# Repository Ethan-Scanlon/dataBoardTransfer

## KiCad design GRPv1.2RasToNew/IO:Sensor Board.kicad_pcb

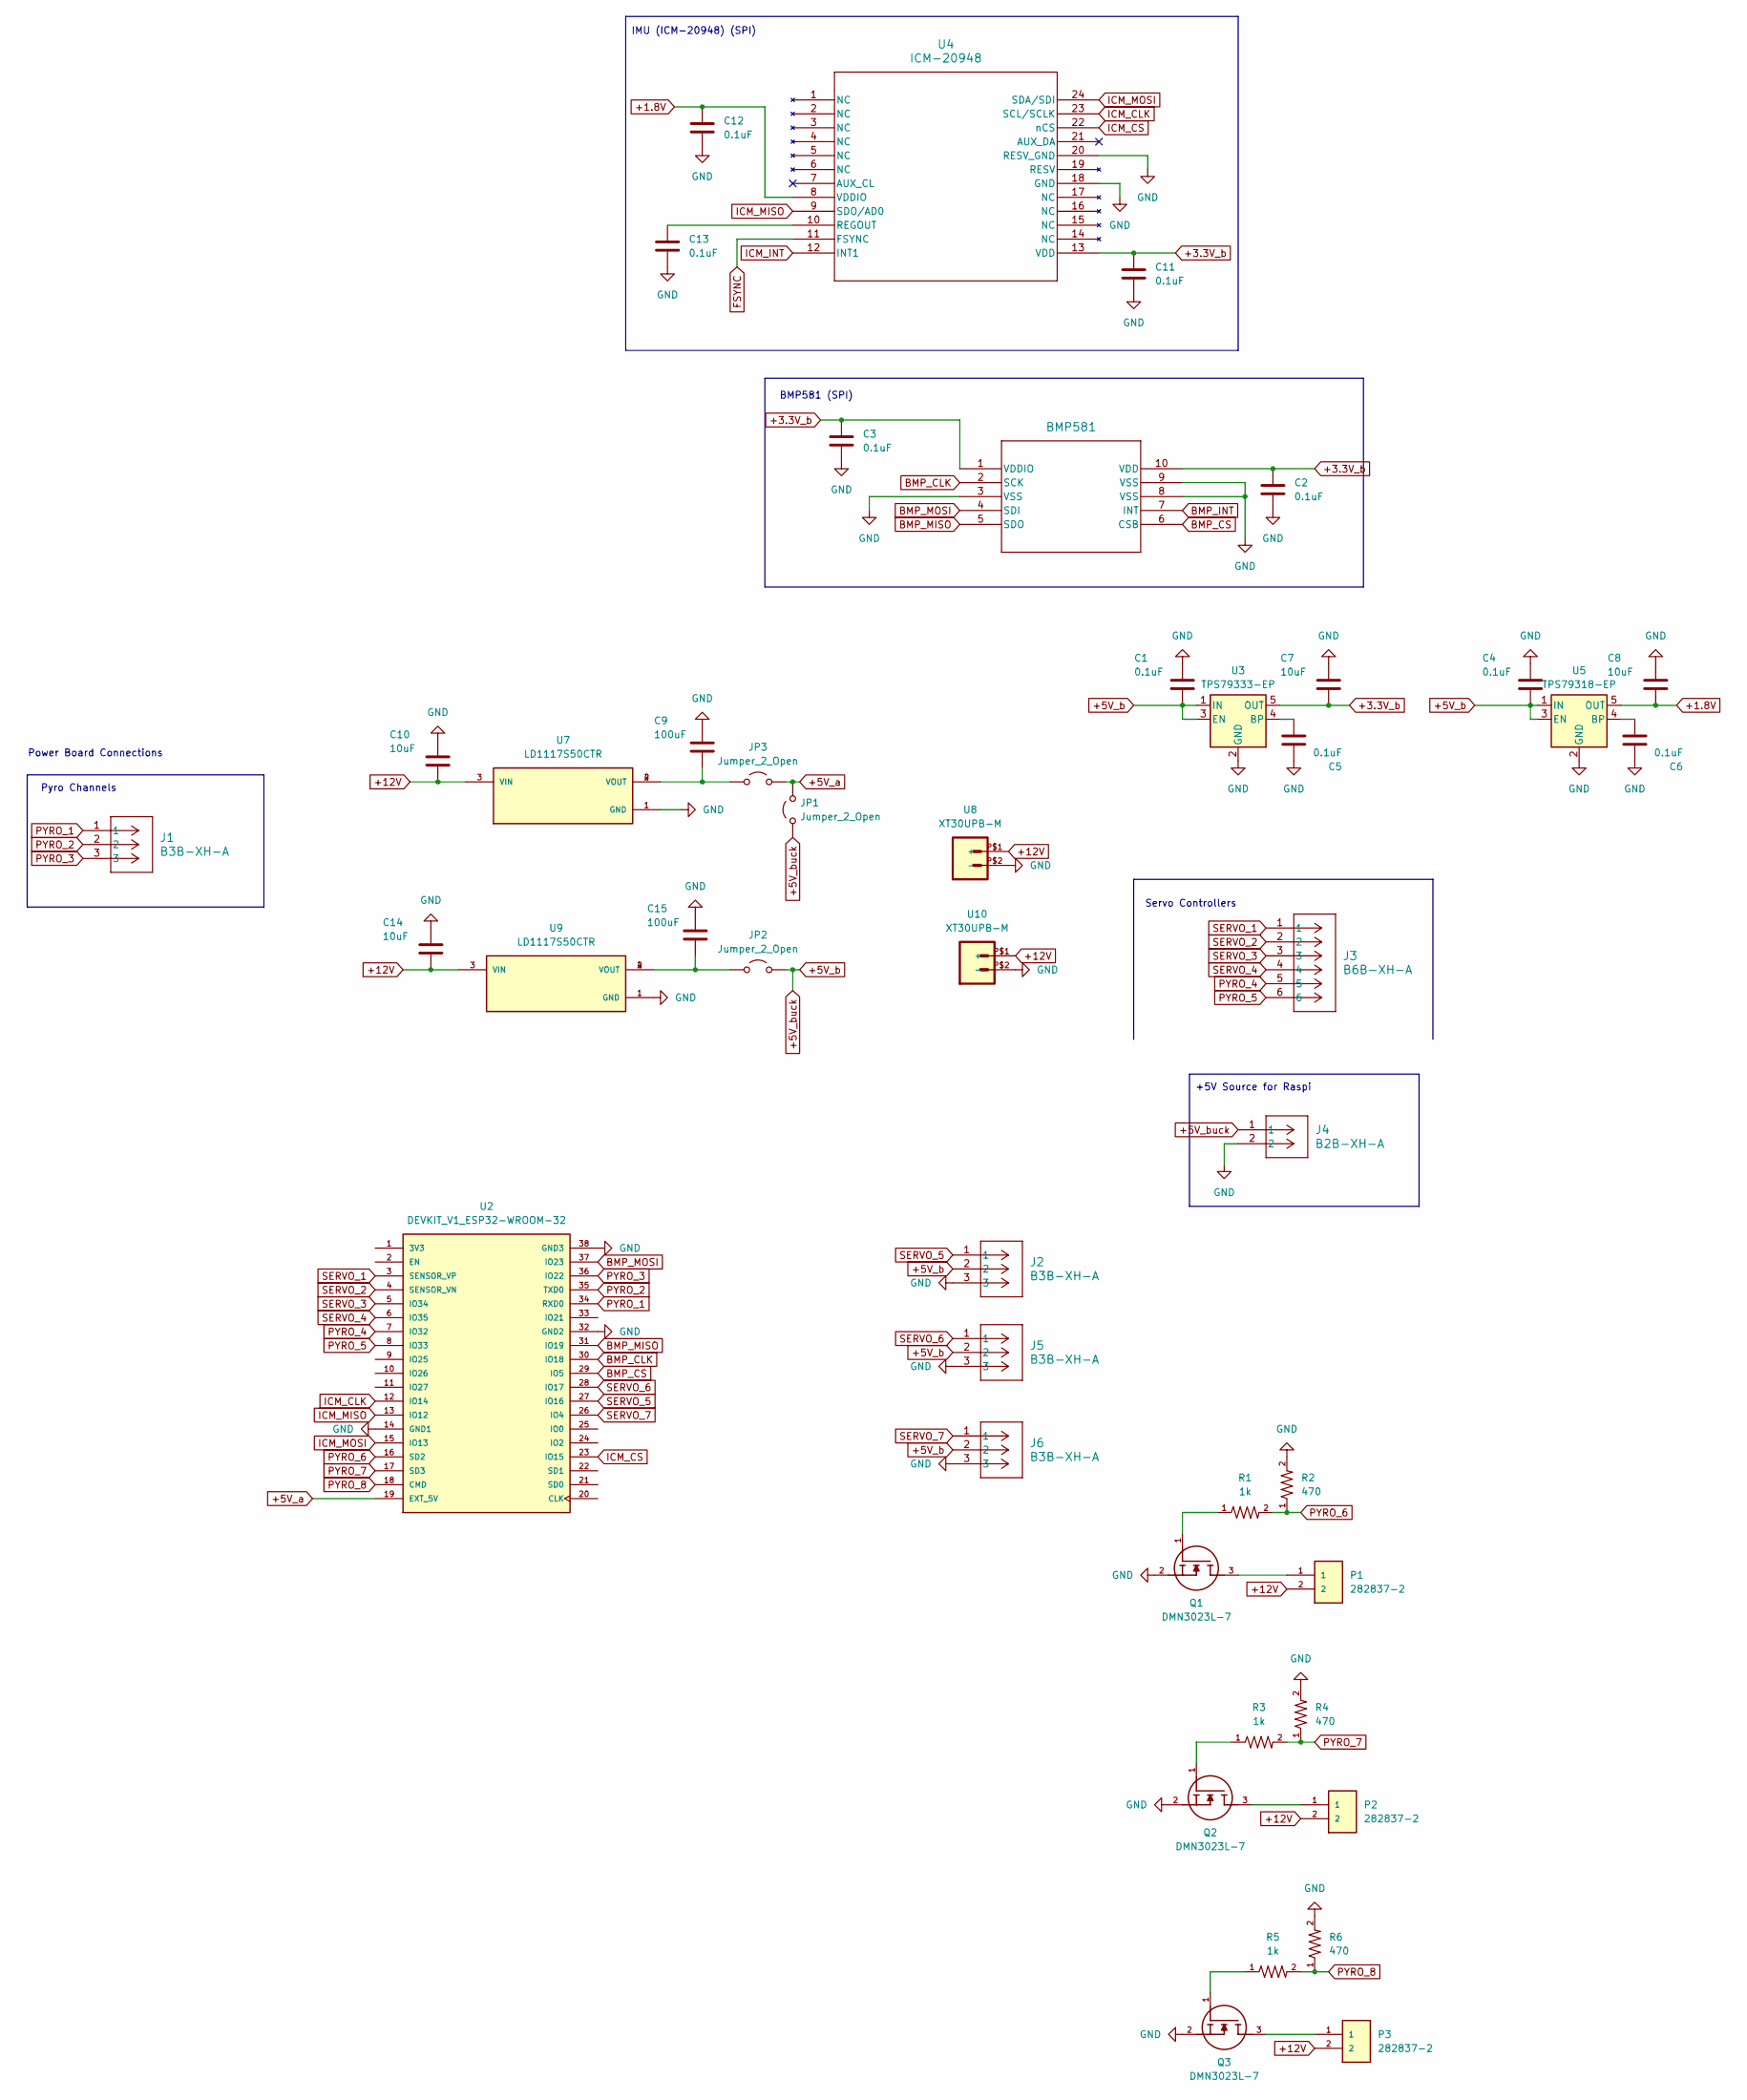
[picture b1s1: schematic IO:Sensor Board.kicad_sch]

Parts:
C1, C2, C3, C4, C5, C6, C11, C12, C13: 0.1uF; C_0805_2012Metric_Pad1.18x1.45mm_HandSolder
C7, C8, C10, C14: 10uF; C_0805_2012Metric_Pad1.18x1.45mm_HandSolder
C9, C15: 100uF; C_0805_2012Metric_Pad1.18x1.45mm_HandSolder
J1, J2, J5, J6: B3B-XH-A; CONN_B3B-XH-A_JST
J3: B6B-XH-A; JST_XH_B6B-XH-A_1x06_P2.50mm_Vertical
J4: B2B-XH-A; CONN_B2B-XH-A_JST
JP1, JP2, JP3: Jumper_2_Open; SolderJumper-2_P1.3mm_Open_RoundedPad1.0x1.5mm
P1, P2, P3: 282837-2; CUI_TB002-500-02BE; PARTREV G3
Q1, Q2, Q3: DMN3023L-7; SOT96P240X100-3N; MANUFACTURER_PART_NUMBER DMN3023L-7
R1, R3, R5: 1k; R_0805_2012Metric_Pad1.20x1.40mm_HandSolder
R2, R4, R6: 470; R_0805_2012Metric_Pad1.20x1.40mm_HandSolder
U1: BMP581; QFN10_BMP581_BOS
U2: DEVKIT_V1_ESP32-WROOM-32; MODULE_DEVKIT_V1_ESP32-WROOM-32; PARTREV N/A
U3: TPS79333-EP; SOT-23-5
U4: ICM-20948; QFN24_3X3X0P9_IVS
U5: TPS79318-EP; SOT-23-5
U7, U9: LD1117S50CTR; PARTREV 37
U8, U10: XT30UPB-M

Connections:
+1.8V: C8.2, C12.1, U4.8 (VDDIO), U5.5 (OUT)
+3.3V_b: C2.1, C3.1, C7.2, C11.1, U1.1 (VDDIO), U1.10 (VDD), U3.5 (OUT), U4.13 (VDD)
+5V_a: JP1.2 (B), JP3.2 (B), U2.19 (EXT_5V)
+5V_b: C1.2, C4.2, J2.2, J4.1, J5.2, J6.2, JP1.1 (A), JP2.2 (B), U3.1 (IN), U3.3 (EN), U5.1 (IN), U5.3 (EN)
+12V: C10.2, C14.2, P1.2, P2.2, P3.2, U7.3 (VIN), U8.P$1 (+), U9.3 (VIN), U10.P$1 (+)
BMP_CLK: U1.2 (SCK), U2.30 (IO18)
BMP_CS: U1.6 (CSB), U2.29 (IO5)
BMP_INT: U1.7 (INT)
BMP_MISO: U1.5 (SDO), U2.31 (IO19)
BMP_MOSI: U1.4 (SDI), U2.37 (IO23)
FSYNC: U4.11 (FSYNC)
GND: C1.1, C2.2, C3.2, C4.1, C5.1, C6.1, C7.1, C8.1, C9.1, C10.1, C11.2, C12.2, C13.2, C14.1, C15.1, J2.3, J4.2, J5.3, J6.3, Q1.2, Q2.2, Q3.2, R2.2, R4.2, R6.2, U1.3 (VSS), U1.8 (VSS), U1.9 (VSS), U2.14 (GND1), U2.32 (GND2), U2.38 (GND3), U3.2 (GND), U4.18 (GND), U4.20 (RESV_GND), U5.2 (GND), U7.1 (GND), U8.P$2 (-), U9.1 (GND), U10.P$2 (-)
ICM_CLK: U2.12 (IO14), U4.23 (SCL/SCLK)
ICM_CS: U2.23 (IO15), U4.22 (nCS)
ICM_INT: U4.12 (INT1)
ICM_MISO: U2.13 (IO12), U4.9 (SDO/AD0)
ICM_MOSI: U2.15 (IO13), U4.24 (SDA/SDI)
unnamed: C15.2, JP2.1 (A), U9.2 (VOUT), U9.4 (VOUT)
unnamed: C9.2, JP3.1 (A), U7.2 (VOUT), U7.4 (VOUT)
unnamed: P1.1, Q1.3
unnamed: P2.1, Q2.3
unnamed: P3.1, Q3.3
unnamed: Q1.1, R1.1
unnamed: Q2.1, R3.1
unnamed: Q3.1, R5.1
unnamed: C5.2, U3.4 (BP)
unnamed: C13.1, U4.10 (REGOUT)
unnamed: C6.2, U5.4 (BP)
PYRO_1: J1.1, U2.34 (RXD0)
PYRO_2: J1.2, U2.35 (TXD0)
PYRO_3: J1.3, U2.36 (IO22)
PYRO_4: J3.5, U2.7 (IO32)
PYRO_5: J3.6, U2.8 (IO33)
PYRO_6: R1.2, R2.1, U2.16 (SD2)
PYRO_7: R3.2, R4.1, U2.17 (SD3)
PYRO_8: R5.2, R6.1, U2.18 (CMD)
SERVO_1: J3.1, U2.3 (SENSOR_VP)
SERVO_2: J3.2, U2.4 (SENSOR_VN)
SERVO_3: J3.3, U2.5 (IO34)
SERVO_4: J3.4, U2.6 (IO35)
SERVO_5: J2.1, U2.27 (IO16)
SERVO_6: J5.1, U2.28 (IO17)
SERVO_7: J6.1, U2.26 (IO4)

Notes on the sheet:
+5V Source for Raspi
Pyro Channels
BMP581 (SPI)
IMU (ICM-20948) (SPI)
Power Board Connections
Servo Controllers

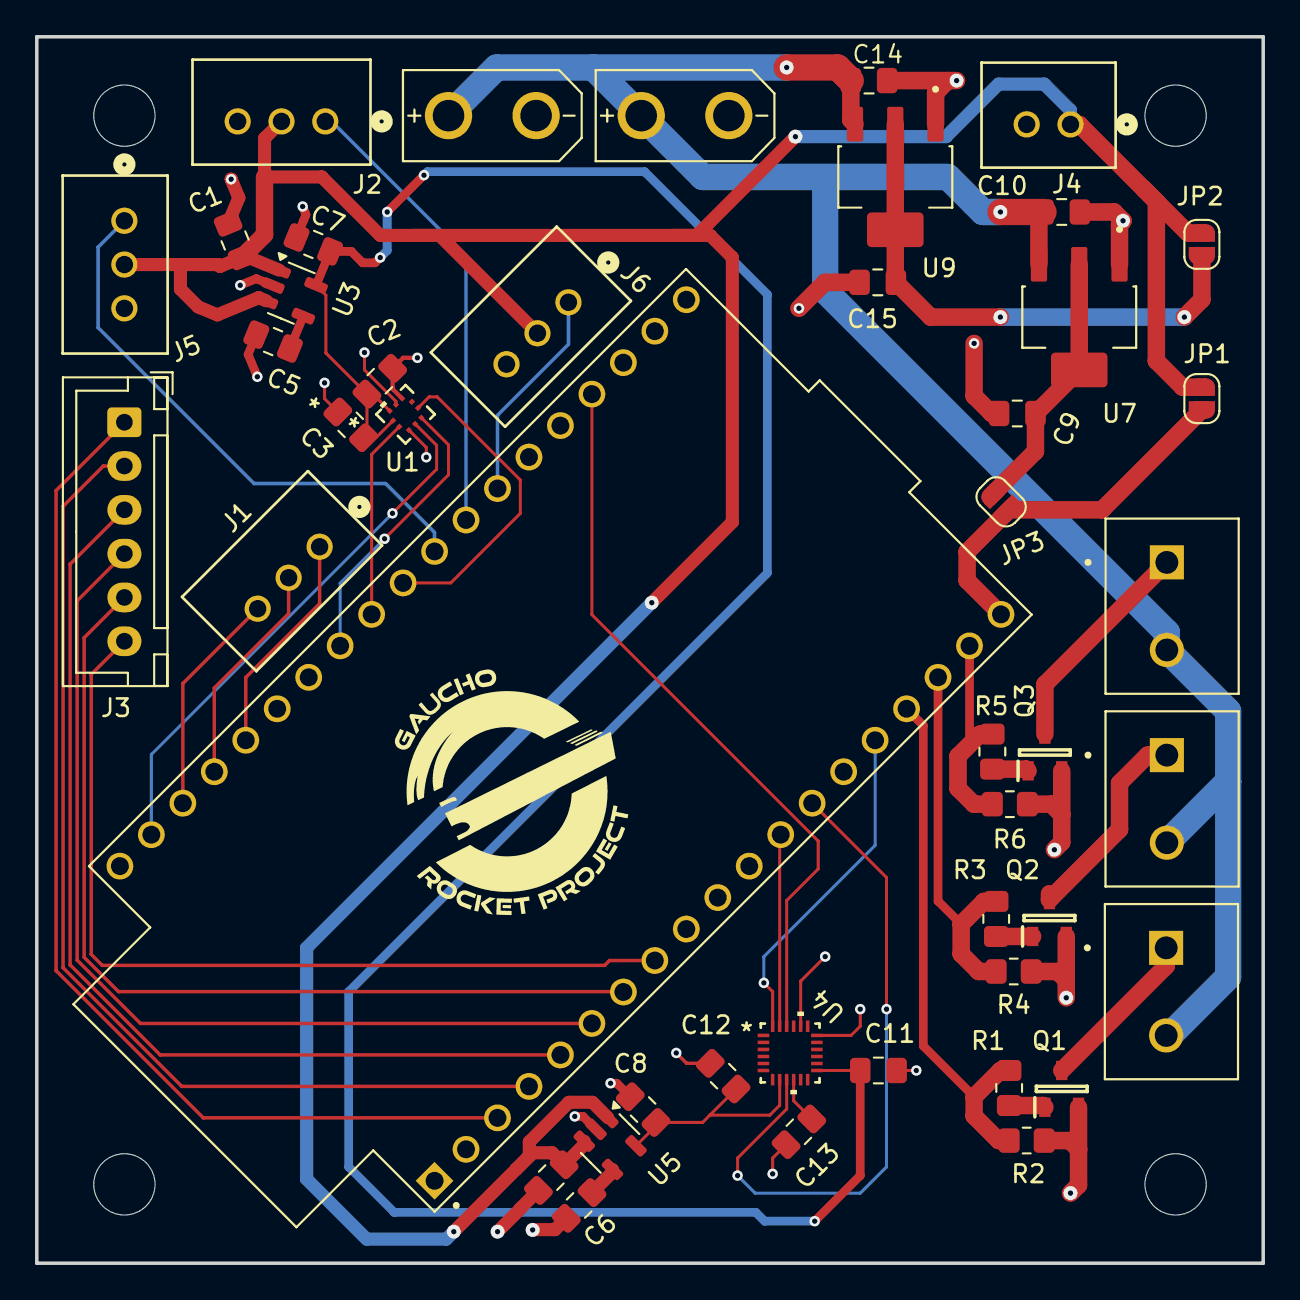
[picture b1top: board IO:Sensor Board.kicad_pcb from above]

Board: 4 copper layers, 70.0 x 70.0 mm, 45 parts (0 on the bottom side), 40 nets.

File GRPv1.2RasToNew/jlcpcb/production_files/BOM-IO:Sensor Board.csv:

Comment,Designator,Footprint,LCSC,Quantity
B3B-XH-A,"J1,J2,J5,J6",CONN_B3B-XH-A_JST,C144394,4
B6B-XH-A,J3,JST_XH_B6B-XH-A_1x06_P2.50mm_Vertical,C144397,1
B2B-XH-A,J4,CONN_B2B-XH-A_JST,C158012,1
10uF,"C10,C14,C7,C8",C_0805_2012Metric_Pad1.18x1.45mm_HandSolder,C15850,4
1k,"R1,R3,R5",R_0805_2012Metric_Pad1.20x1.40mm_HandSolder,C17513,3
470,"R2,R4,R6",R_0805_2012Metric_Pad1.20x1.40mm_HandSolder,C17710,3
0.1uF,"C1,C11,C12,C13,C15,C2,C3,C4,C5,C6,C9",C_0805_2012Metric_Pad1.18x1.45mm_HandSolder,C28233,11
DMN3023L-7,"Q1,Q2,Q3",SOT96P240X100-3N,C443825,3
BMP581,U1,QFN10_BMP581_BOS,C5362283,1
TPS79318-EP,U5,SOT-23-5,C7102,1
ICM-20948,U4,QFN24_3X3X0P9_IVS,C726001,1
LD1117S50CTR,"U7,U9",LD1117S50CTR,C81157,2
282837-2,"P1,P2,P3",CUI_TB002-500-02BE,C8269,3
TPS79333-EP,U3,SOT-23-5,C9840,1
XT30UPB-M,"U10,U8",XT30UPB-M,C99101,2
Jumper_2_Open,JP3,SolderJumper-2_P1.3mm_Open_RoundedPad1.0x1.5mm,,1
Jumper_2_Open,JP2,SolderJumper-2_P1.3mm_Open_RoundedPad1.0x1.5mm,,1
DEVKIT_V1_ESP32-WROOM-32,U2,MODULE_DEVKIT_V1_ESP32-WROOM-32,,1
Jumper_2_Open,JP1,SolderJumper-2_P1.3mm_Open_RoundedPad1.0x1.5mm,,1

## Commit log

2025-04-14 Inital Commit
2025-04-14 teensy modification
2025-04-15 esp switch 1
2025-04-15 save 2
2025-04-16 check off
2025-04-16 checkoff with pwm
2025-04-16 hope
2025-04-16 hope again
2025-04-17 oops
